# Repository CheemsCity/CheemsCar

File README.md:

# CheemsCar
## Il nostro robot studiato per imparare la robotica da zero

La CheemsCar è un robot open source, modulare e facilmente costruibile. Utilizza componenti tagliati al laser e stampati in 3D, oltre che un Arduino Uno (con una particolare Arduino Shield progettata da noi) e un Rasperry Pi. La CheemsCar è in grado di guidare in una strada, riconoscere cartelli e non investire i CyberCheems (pedoni). Inoltre è progettata per poter facilmente aggiungere funzionalità, quindi il limite è solo la vostra fantasia!

## Cosa necessiti per costruirlo?
- Bill of materials:
- 3D printed parts:
- Laser cut parts:
- [Arduino Shield](./PCB)

## Assembling:
Segui la guida step-by-step:

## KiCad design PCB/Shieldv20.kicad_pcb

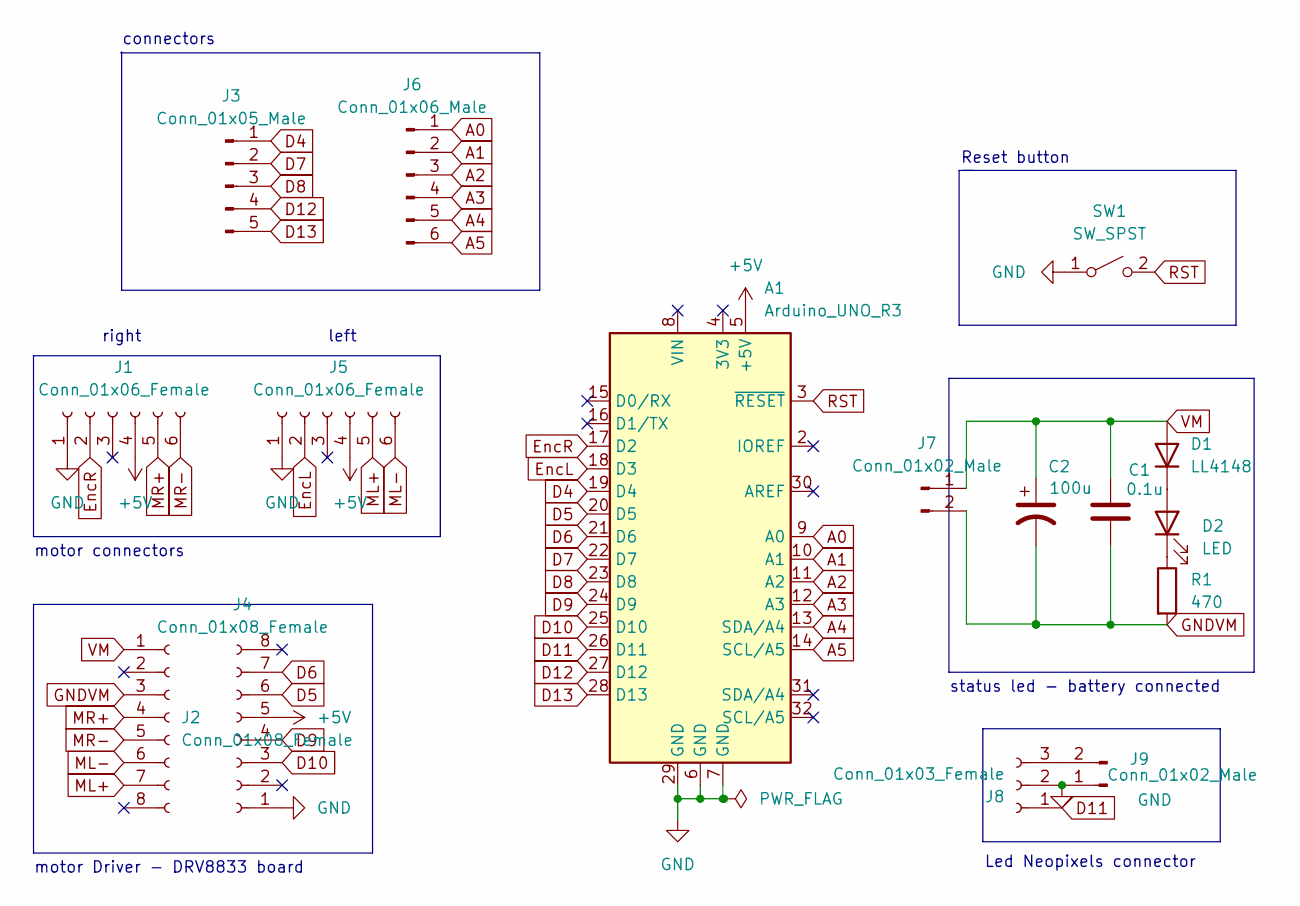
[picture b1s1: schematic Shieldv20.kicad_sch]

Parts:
A1: Arduino_UNO_R3
C1: 0.1u; C_0402_1005Metric
C2: 100u; CP_Elec_6.3x5.4
D1: LL4148; D_SOD-123
D2: LED; LED_0805_2012Metric
J1, J5: Conn_01x06_Female; JST_PH_S6B-PH-K_1x06_P2.00mm_Horizontal
J2, J4: Conn_01x08_Female; PinSocket_1x08_P2.54mm_Vertical
J3: Conn_01x05_Male; PinHeader_1x05_P2.54mm_Vertical
J6: Conn_01x06_Male; PinHeader_1x06_P2.54mm_Vertical
J7, J9: Conn_01x02_Male; PinHeader_1x02_P2.54mm_Vertical
J8: Conn_01x03_Female; JST_PH_S3B-PH-K_1x03_P2.00mm_Horizontal
R1: 470; R_0805_2012Metric
SW1: SW_SPST; SW_PUSH_6mm

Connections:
+5V: A1.5 (+5V), J1.4, J4.5, J5.4
A0: A1.9 (A0), J6.1
A1: A1.10 (A1), J6.2
A2: A1.11 (A2), J6.3
A3: A1.12 (A3), J6.4
A4: A1.13 (SDA/A4), J6.5
A5: A1.14 (SCL/A5), J6.6
D4: A1.19 (D4), J3.1
D5: A1.20 (D5), J4.6
D6: A1.21 (D6), J4.7
D7: A1.22 (D7), J3.2
D8: A1.23 (D8), J3.3
D9: A1.24 (D9), J4.4
D10: A1.25 (D10), J4.3
D11: A1.26 (D11), J8.1
D12: A1.27 (D12), J3.4
D13: A1.28 (D13), J3.5
EncL: A1.18 (D3), J5.2
EncR: A1.17 (D2), J1.2
GND: A1.6 (GND), A1.7 (GND), A1.29 (GND), J1.1, J4.1, J5.1, J8.2, J9.1, SW1.1 (A)
GNDVM: C1.2, C2.2, J2.3, J7.2, R1.2
ML+: J2.7, J5.5
ML-: J2.6, J5.6
MR+: J1.5, J2.4
MR-: J1.6, J2.5
unnamed: D1.1 (K), D2.2 (A)
unnamed: D2.1 (K), R1.1
unnamed: J8.3, J9.2
RST: A1.3 (~RESET), SW1.2 (B)
VM: C1.1, C2.1, D1.2 (A), J2.1, J7.1

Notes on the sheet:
motor Driver - DRV8833 board
left
connectors
right
status led - battery connected
motor connectors
Led Neopixels connector
Reset button

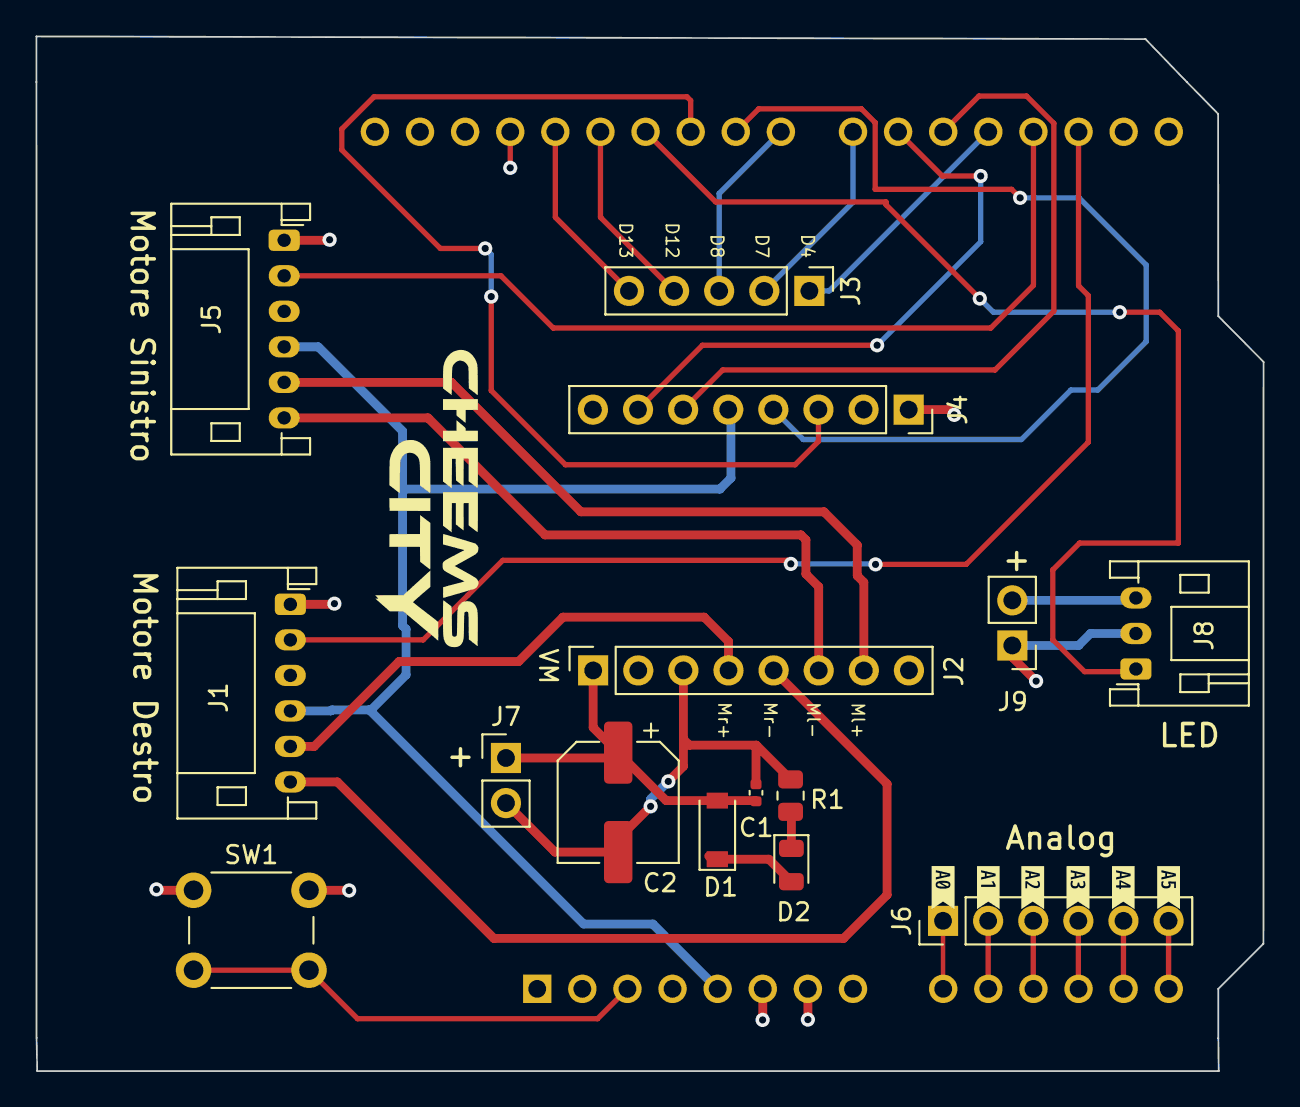
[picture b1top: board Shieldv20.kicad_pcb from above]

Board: 2 copper layers, 69.1 x 58.3 mm, 22 parts (1 on the bottom side), 30 nets.

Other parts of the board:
kibuzzard-64EEFEBA: G***; kibuzzard-64EEFEBA
kibuzzard-64EEFF4B: G***; kibuzzard-64EEFF4B
kibuzzard-64EEFF9E: G***; kibuzzard-64EEFF9E
kibuzzard-64EEFF44: G***; kibuzzard-64EEFF44
kibuzzard-64EEFF65: G***; kibuzzard-64EEFF65
kibuzzard-64EEFF81: G***; kibuzzard-64EEFF81

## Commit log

2023-09-10 start
2023-09-10 start2
2024-03-20 add files 3d
    add file 3d
